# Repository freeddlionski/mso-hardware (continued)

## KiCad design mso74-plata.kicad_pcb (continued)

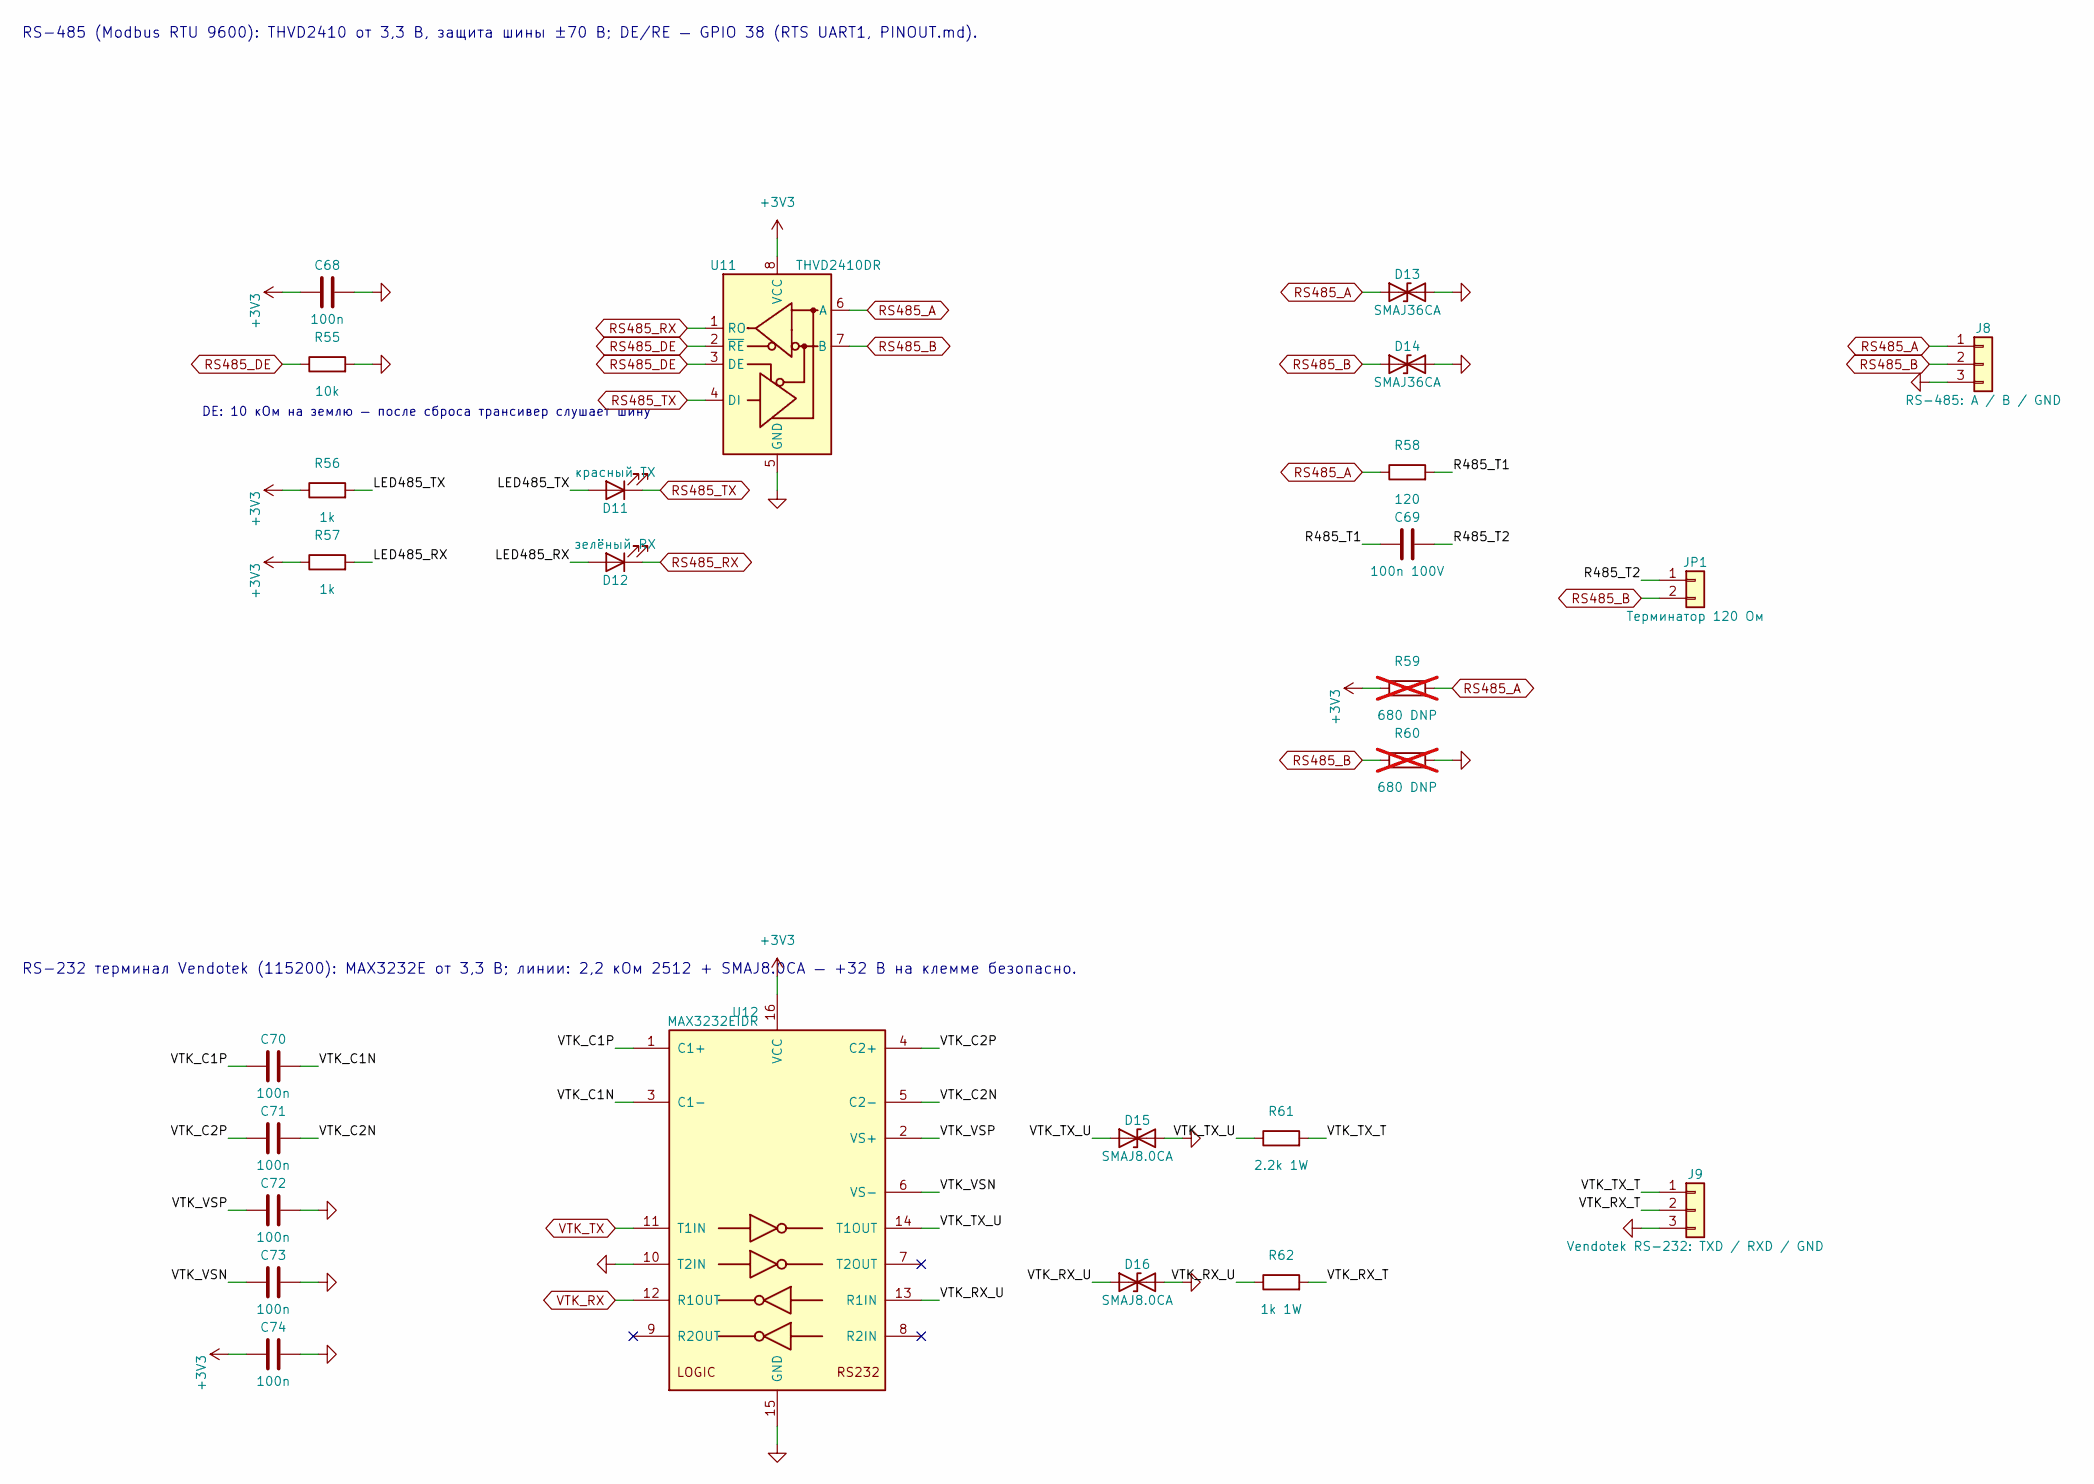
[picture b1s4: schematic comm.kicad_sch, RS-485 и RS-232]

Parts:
C68, C70, C71, C72, C73, C74: 100n; C_0603_1608Metric; MPN CC0603KRX7R9BB104; LCSC C14663
C69: 100n 100V; C_0805_2012Metric; MPN TCC0805X7R104K101DT; LCSC C344180
D11: красный TX; LED_0603_1608Metric; LCSC C2286
D12: зелёный RX; LED_0603_1608Metric; MPN KT-0603YG; LCSC C2289
D13, D14: SMAJ36CA; D_SMA; MPN SMAJ36CA; LCSC C5249597
D15, D16: SMAJ8.0CA; D_SMA; MPN SMAJ8.0CA; LCSC C148237
J8: RS-485: A / B / GND; KANGNEX_WJ15EDGRC_1x03_P3.81mm_Drill1.4; MPN WJ15EDGRC-3.81-03P-14-00A; LCSC C8406
J9: Vendotek RS-232: TXD / RXD / GND; KANGNEX_WJ15EDGRC_1x03_P3.81mm_Drill1.4; MPN WJ15EDGRC-3.81-03P-14-00A; LCSC C8406
JP1: Терминатор 120 Ом; PinHeader_1x02_P2.54mm_Vertical; MPN PZ254V-11-02P; LCSC C492401
R55: 10k; R_0603_1608Metric; MPN 0603WAF1002T5E; LCSC C25804
R56, R57: 1k; R_0603_1608Metric; MPN 0603WAF1001T5E; LCSC C21190
R58: 120; R_0805_2012Metric; MPN 0805W8F1200T5E; LCSC C17437
R59, R60: 680 DNP; R_0603_1608Metric; MPN 0603WAF6800T5E; LCSC C23228; not fitted
R61: 2.2k 1W; R_2512_6332Metric; MPN RC-12K2201FT; LCSC C453411
R62: 1k 1W; R_2512_6332Metric; MPN RC-12K1001FT; LCSC C453362
U11: THVD2410DR; SOIC-8_3.9x4.9mm_P1.27mm; MPN THVD2410DR; LCSC C1849398
U12: MAX3232EIDR; SOIC-16_3.9x9.9mm_P1.27mm; MPN MAX3232EIDR; LCSC C193666

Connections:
+3V3: C68.1, C74.1, R56.1, R57.1, R59.1, U11.8 (VCC), U12.16 (VCC); also elsewhere on the board
/RS-485 и RS-232/LED485_RX: D12.2 (A), R57.2
/RS-485 и RS-232/LED485_TX: D11.2 (A), R56.2
/RS-485 и RS-232/R485_T1: C69.1, R58.2
/RS-485 и RS-232/R485_T2: C69.2, JP1.1
/RS-485 и RS-232/VTK_C1N: C70.2, U12.3 (C1-)
/RS-485 и RS-232/VTK_C1P: C70.1, U12.1 (C1+)
/RS-485 и RS-232/VTK_C2N: C71.2, U12.5 (C2-)
/RS-485 и RS-232/VTK_C2P: C71.1, U12.4 (C2+)
/RS-485 и RS-232/VTK_RX_T: J9.2, R62.2
/RS-485 и RS-232/VTK_RX_U: D16.1 (A1), R62.1, U12.13 (R1IN)
/RS-485 и RS-232/VTK_TX_T: J9.1, R61.2
/RS-485 и RS-232/VTK_TX_U: D15.1 (A1), R61.1, U12.14 (T1OUT)
/RS-485 и RS-232/VTK_VSN: C73.1, U12.6 (VS-)
/RS-485 и RS-232/VTK_VSP: C72.1, U12.2 (VS+)
GND: C68.2, C72.2, C73.2, C74.2, D13.2 (A2), D14.2 (A2), D15.2 (A2), D16.2 (A2), J8.3, J9.3, R55.2, R60.2, U11.5 (GND), U12.10 (T2IN), U12.15 (GND); also elsewhere on the board
RS485_A: D13.1 (A1), J8.1, R58.1, R59.2, U11.6 (A); also elsewhere on the board
RS485_B: D14.1 (A1), J8.2, JP1.2, R60.1, U11.7 (B); also elsewhere on the board
RS485_DE: R55.1, U11.2 (~RE), U11.3 (DE); also elsewhere on the board
RS485_RX: D12.1 (K), U11.1 (RO); also elsewhere on the board
RS485_TX: D11.1 (K), U11.4 (DI); also elsewhere on the board
VTK_RX: U12.12 (R1OUT); also elsewhere on the board
VTK_TX: U12.11 (T1IN); also elsewhere on the board

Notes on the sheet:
RS-485 (Modbus RTU 9600): THVD2410 от 3,3 В, защита шины ±70 В; DE/RE — GPIO 38 (RTS UART1, PINOUT.md).
DE: 10 кОм на землю — после сброса трансивер слушает шину
RS-232 терминал Vendotek (115200): MAX3232E от 3,3 В; линии: 2,2 кОм 2512 + SMAJ8.0CA — +32 В на клемме безопасно.

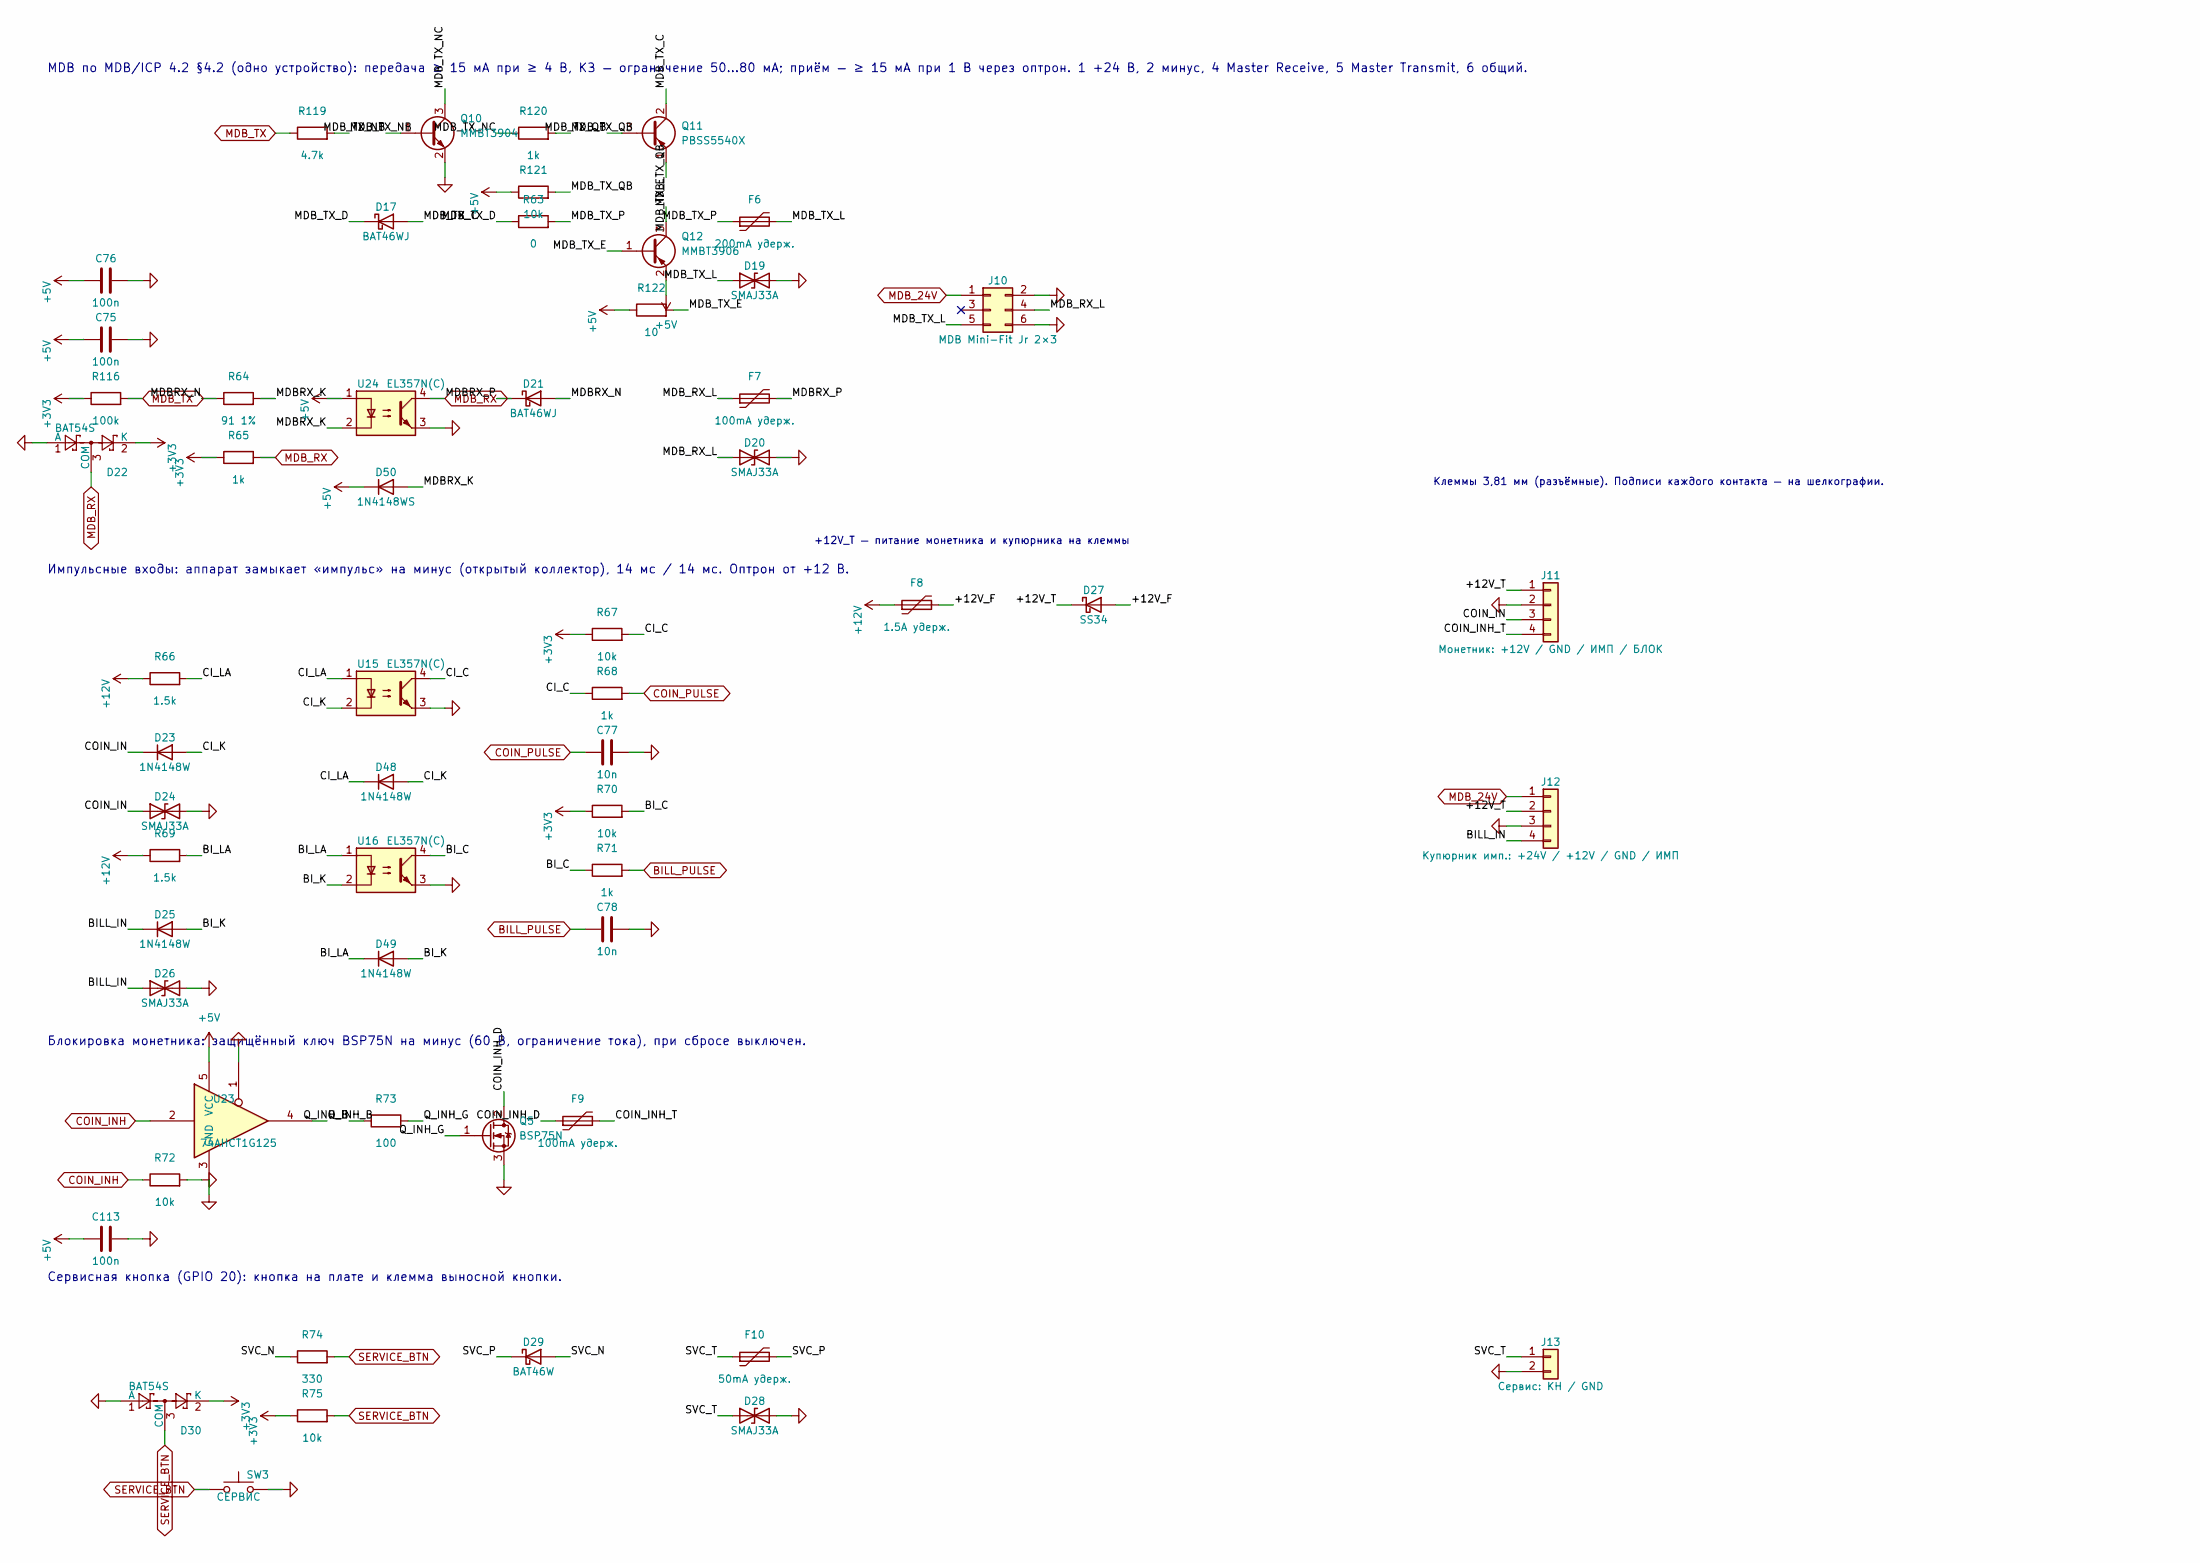
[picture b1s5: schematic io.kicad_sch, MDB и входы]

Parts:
C75, C76, C113: 100n; C_0603_1608Metric; MPN CC0603KRX7R9BB104; LCSC C14663
C77, C78: 10n; C_0603_1608Metric; MPN 0603B103K500NT; LCSC C57112
D17, D21: BAT46WJ; D_SOD-323F; MPN BAT46WJ,115; LCSC C114696
D19, D20, D24, D26, D28: SMAJ33A; D_SMA; MPN SMAJ33A; LCSC C223988
D22, D30: BAT54S; SOT-23; MPN BAT54S; LCSC C47546
D23, D25, D48, D49: 1N4148W; D_SOD-123; MPN 1N4148W; LCSC C81598
D27: SS34; D_SMA; MPN SS34; LCSC C8678
D29: BAT46W; D_SOD-123; MPN BAT46W; LCSC C7420332
D50: 1N4148WS; D_SOD-323; MPN 1N4148WS; LCSC C2128
F6: 200mA удерж.; Fuse_1812_4532Metric; MPN 1812L020/60DR; LCSC C315900
F7, F9: 100mA удерж.; Fuse_1206_3216Metric; MPN nSMD010; LCSC C70065
F8: 1.5A удерж.; Fuse_2920_7451Metric; MPN SMD2920-150/60N; LCSC C6165178
F10: 50mA удерж.; Fuse_1206_3216Metric; MPN 1206L005/60WR; LCSC C315892
J10: MDB Mini-Fit Jr 2×3; Molex_Mini-Fit_Jr_5566-06A_2x03_P4.20mm_Vertical; MPN Molex 5566-06A; LCSC C20539148
J11: Монетник: +12V / GND / ИМП / БЛОК; KANGNEX_WJ15EDGRC_1x04_P3.81mm_Drill1.4; MPN WJ15EDGRC-3.81-04P-14-00A; LCSC C7245
J12: Купюрник имп.: +24V / +12V / GND / ИМП; KANGNEX_WJ15EDGRC_1x04_P3.81mm_Drill1.4; MPN WJ15EDGRC-3.81-04P-14-00A; LCSC C7245
J13: Сервис: КН / GND; KANGNEX_WJ15EDGRC_1x02_P3.81mm_Drill1.4; MPN WJ15EDGRC-3.81-02P-14-00A; LCSC C8387
Q5: BSP75N; SOT-223-3_TabPin3_BSP75N; MPN BSP75N; LCSC C114056
Q10: MMBT3904; SOT-23; MPN MMBT3904; LCSC C20526
Q11: PBSS5540X; SOT-89-3; MPN PBSS5540X,135; LCSC C455078
Q12: MMBT3906; SOT-23; MPN MMBT3906; LCSC C916375
R63: 0; R_0805_2012Metric; MPN 0805W8F0000T5E; LCSC C17477
R64: 91 1%; R_1206_3216Metric; MPN RC1206FR-0791RL; LCSC C137223
R65, R68, R71, R120: 1k; R_0603_1608Metric; MPN 0603WAF1001T5E; LCSC C21190
R66, R69: 1.5k; R_0603_1608Metric; MPN 0603WAF1501T5E; LCSC C22843
R67, R70, R72, R75, R121: 10k; R_0603_1608Metric; MPN 0603WAF1002T5E; LCSC C25804
R73: 100; R_0603_1608Metric; MPN 0603WAF1000T5E; LCSC C22775
R74: 330; R_0603_1608Metric; MPN 0603WAF3300T5E; LCSC C23138
R116: 100k; R_0603_1608Metric; MPN 0603WAF1003T5E; LCSC C25803
R119: 4.7k; R_0603_1608Metric; MPN 0603WAF4701T5E; LCSC C23162
R122: 10; R_0805_2012Metric; MPN 0805W8F100JT5E; LCSC C17415
SW3: СЕРВИС; SW_SPST_TL3342; MPN TL3342F450QG; LCSC C2886897
U15, U16, U24: EL357N(C); SOP-4_3.8x4.1mm_P2.54mm; MPN EL357N(C)-G; LCSC C42379244
U23: 74AHCT1G125; SOT-23-5; MPN SN74AHCT1G125DBVR; LCSC C7484

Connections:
+3V3: D22.2 (K), D30.2 (K), R65.1, R67.1, R70.1, R75.1, R116.1; also elsewhere on the board
+5V: C75.1, C76.1, C113.1, D50.1 (K), Q12.2 (E), R121.1, R122.1, U23.5 (VCC), U24.1; also elsewhere on the board
+12V: F8.1, R66.1, R69.1; also elsewhere on the board
/MDB и входы/+12V_F: D27.2 (A), F8.2
/MDB и входы/+12V_T: D27.1 (K), J11.1, J12.2
/MDB и входы/BILL_IN: D25.1 (K), D26.1 (A1), J12.4
/MDB и входы/BI_C: R70.2, R71.1, U16.4
/MDB и входы/BI_K: D25.2 (A), D49.2 (A), U16.2
/MDB и входы/BI_LA: D49.1 (K), R69.2, U16.1
/MDB и входы/CI_C: R67.2, R68.1, U15.4
/MDB и входы/CI_K: D23.2 (A), D48.2 (A), U15.2
/MDB и входы/CI_LA: D48.1 (K), R66.2, U15.1
/MDB и входы/COIN_IN: D23.1 (K), D24.1 (A1), J11.3
/MDB и входы/COIN_INH_D: F9.1, Q5.2 (D)
/MDB и входы/COIN_INH_T: F9.2, J11.4
/MDB и входы/MDBRX_K: D50.2 (A), R64.2, U24.2
/MDB и входы/MDBRX_N: D21.2 (A), R64.1
/MDB и входы/MDBRX_P: D21.1 (K), F7.2
/MDB и входы/MDB_RX_L: D20.1 (A1), F7.1, J10.4
/MDB и входы/MDB_TX_C: D17.2 (A), Q11.2 (C)
/MDB и входы/MDB_TX_D: D17.1 (K), R63.1
/MDB и входы/MDB_TX_E: Q11.1 (E), Q12.1 (B), R122.2
/MDB и входы/MDB_TX_L: D19.1 (A1), F6.2, J10.5
/MDB и входы/MDB_TX_NB: Q10.1 (B), R119.2
/MDB и входы/MDB_TX_NC: Q10.3 (C), R120.1
/MDB и входы/MDB_TX_P: F6.1, R63.2
/MDB и входы/MDB_TX_QB: Q11.3 (B), Q12.3 (C), R120.2, R121.2
/MDB и входы/Q_INH_B: R73.1, U23.4
/MDB и входы/Q_INH_G: Q5.1 (G), R73.2
/MDB и входы/SVC_N: D29.2 (A), R74.1
/MDB и входы/SVC_P: D29.1 (K), F10.2
/MDB и входы/SVC_T: D28.1 (A1), F10.1, J13.1
BILL_PULSE: C78.1, R71.2; also elsewhere on the board
COIN_INH: R72.1, U23.2; also elsewhere on the board
COIN_PULSE: C77.1, R68.2; also elsewhere on the board
GND: C75.2, C76.2, C77.2, C78.2, C113.2, D19.2 (A2), D20.2 (A2), D22.1 (A), D24.2 (A2), D26.2 (A2), D28.2 (A2), D30.1 (A), J10.2, J10.6, J11.2, J12.3, J13.2, Q5.3 (S), Q10.2 (E), R72.2, SW3.2, U15.3, U16.3, U23.1, U23.3 (GND), U24.3; also elsewhere on the board
MDB_24V: J10.1, J12.1; also elsewhere on the board
MDB_RX: D22.3 (COM), R65.2, U24.4; also elsewhere on the board
MDB_TX: R116.2, R119.1; also elsewhere on the board
SERVICE_BTN: D30.3 (COM), R74.2, R75.2, SW3.1; also elsewhere on the board

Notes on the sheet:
MDB по MDB/ICP 4.2 §4.2 (одно устройство): передача ≥ 15 мА при ≥ 4 В, КЗ — ограничение 50…80 мА; приём — ≥ 15 мА при 1 В через оптрон. 1 +24 В, 2 минус, 4 Master Receive, 5 Master Transmit, 6 общий.
Импульсные входы: аппарат замыкает «импульс» на минус (открытый коллектор), 14 мс / 14 мс. Оптрон от +12 В.
+12V_T — питание монетника и купюрника на клеммы
Блокировка монетника: защищённый ключ BSP75N на минус (60 В, ограничение тока), при сбросе выключен.
Сервисная кнопка (GPIO 20): кнопка на плате и клемма выносной кнопки.
Клеммы 3,81 мм (разъёмные). Подписи каждого контакта — на шелкографии.

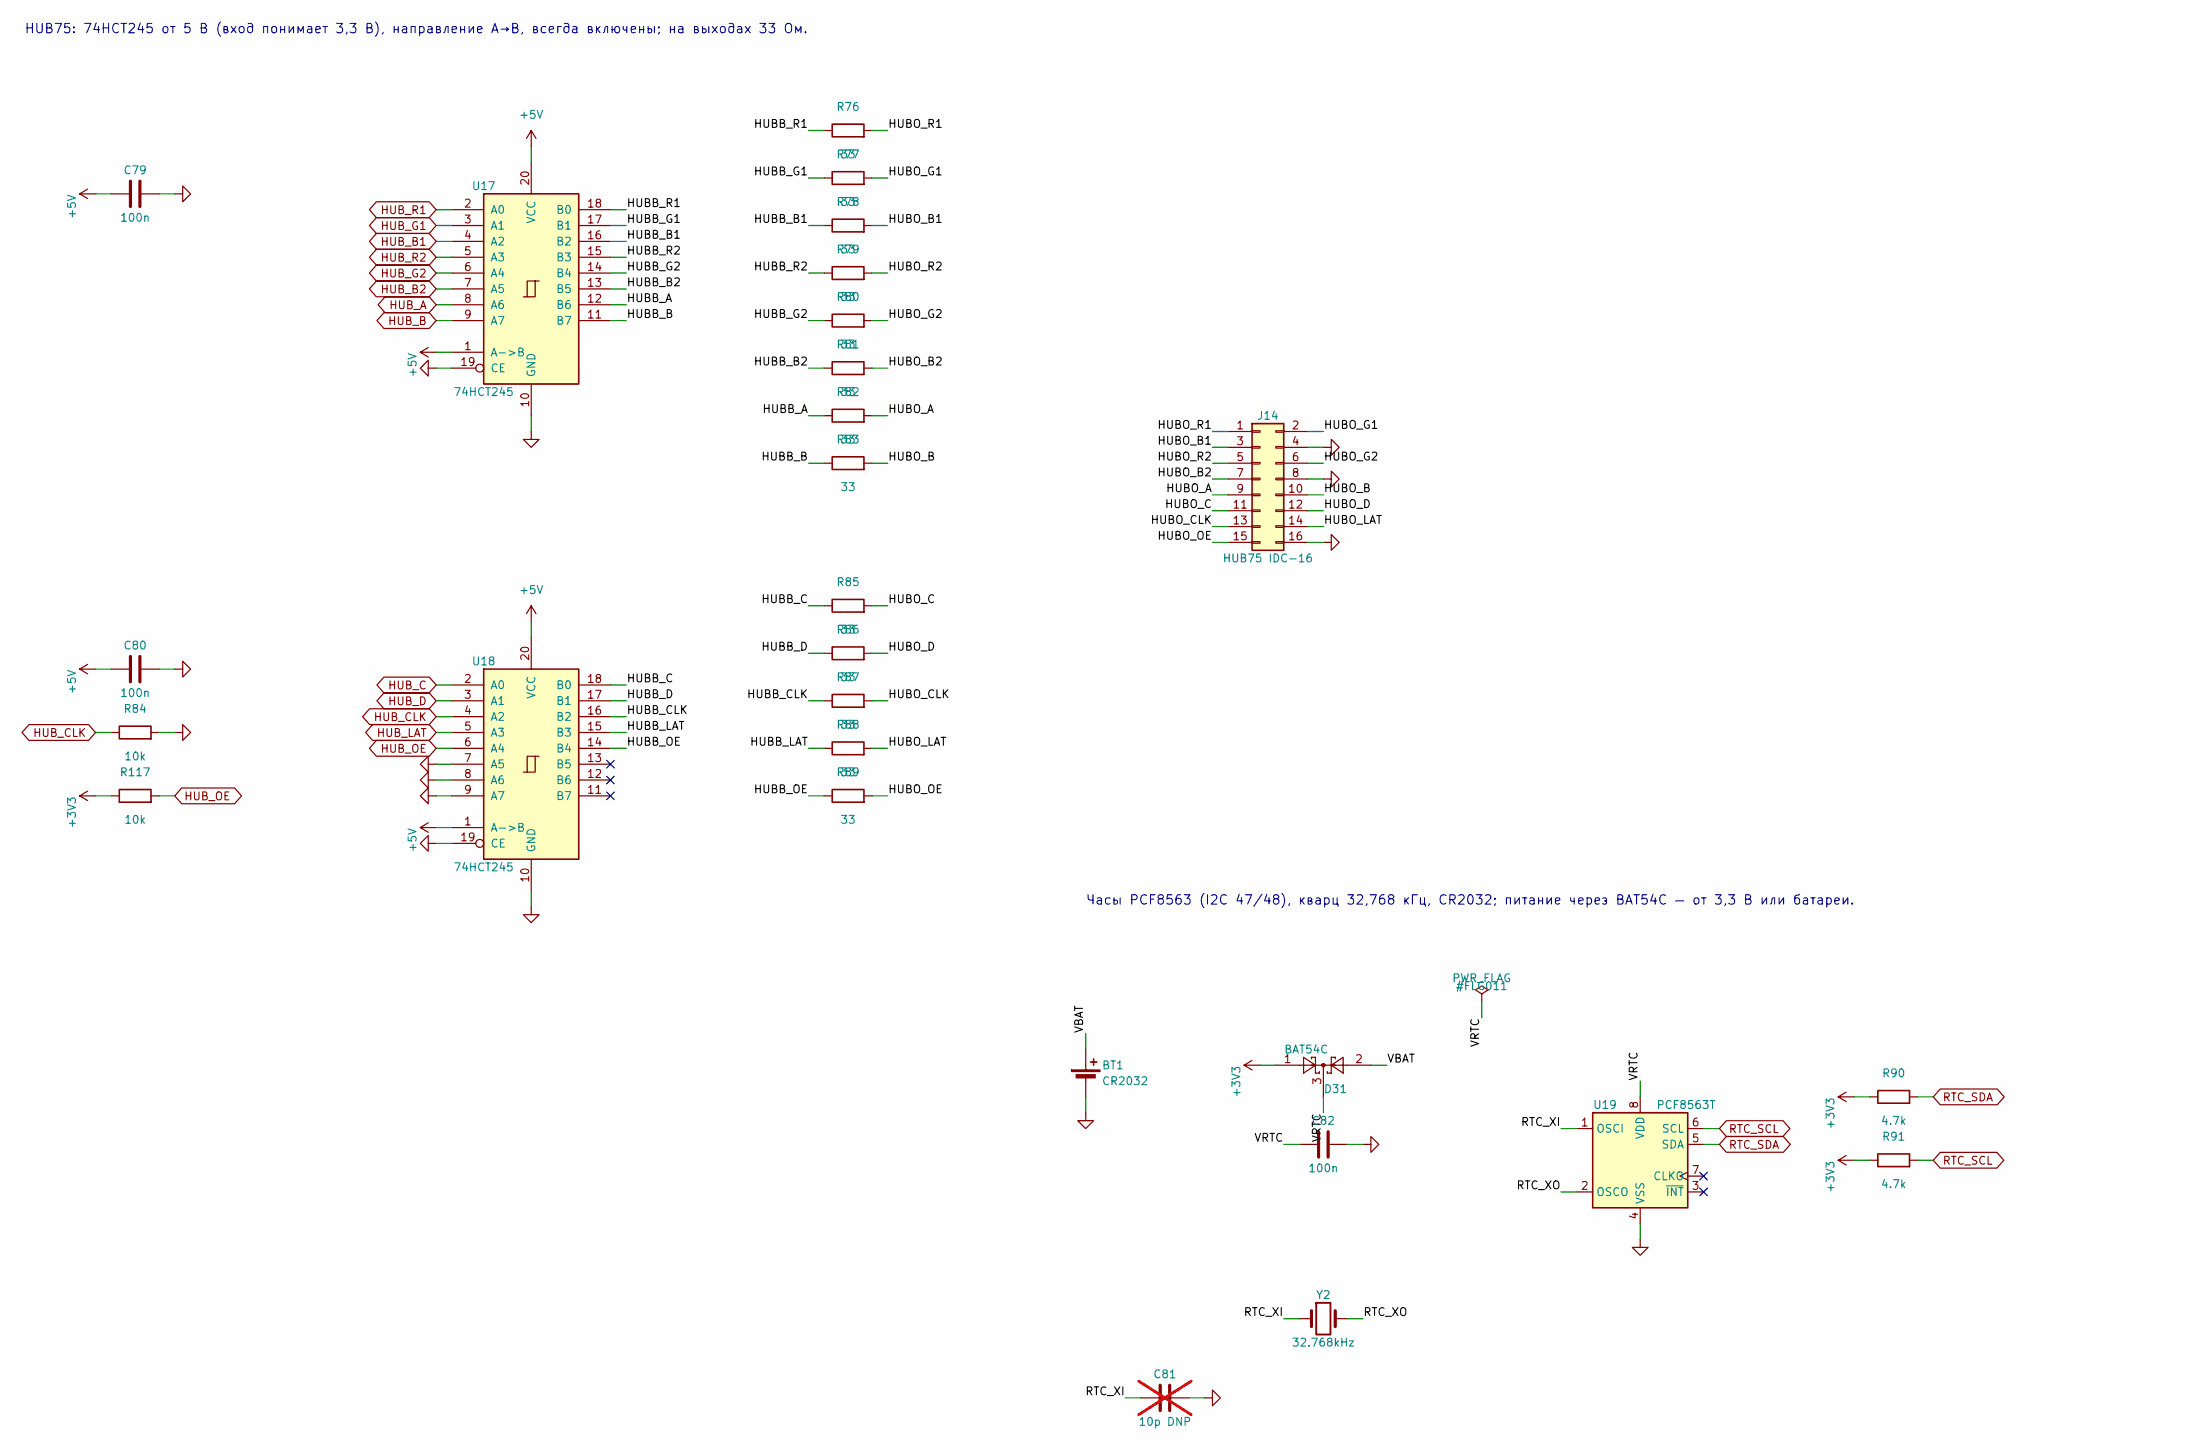
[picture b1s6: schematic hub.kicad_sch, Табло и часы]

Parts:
BT1: CR2032; BatteryHolder_MYOUNG_BS-07-A1BJ001_CR2032; MPN BS-07-A1BJ001; LCSC C2979167
C79, C80, C82: 100n; C_0603_1608Metric; MPN CC0603KRX7R9BB104; LCSC C14663
C81: 10p DNP; C_0603_1608Metric; MPN CL10C100JB8NNNC; LCSC C1634; not fitted
D31: BAT54C; SOT-23; MPN BAT54C; LCSC C2135
J14: HUB75 IDC-16; IDC-Header_2x08_P2.54mm_Vertical; MPN 2.54-2*8P box header; LCSC C3406
R76, R77, R78, R79, R80, R81, R82, R83, R85, R86, R87, R88, R89: 33; R_0603_1608Metric; MPN 0603WAF330JT5E; LCSC C23140
R84, R117: 10k; R_0603_1608Metric; MPN 0603WAF1002T5E; LCSC C25804
R90, R91: 4.7k; R_0603_1608Metric; MPN 0603WAF4701T5E; LCSC C23162
U17, U18: 74HCT245; TSSOP-20_4.4x6.5mm_P0.65mm; MPN 74HCT245PW; LCSC C5980
U19: PCF8563T; SOIC-8_3.9x4.9mm_P1.27mm; MPN PCF8563T/5; LCSC C7440
Y2: 32.768kHz; Crystal_SMD_3215-2Pin_3.2x1.5mm; MPN Q13FC13500004; LCSC C32346

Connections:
+3V3: D31.1, R90.1, R91.1, R117.1; also elsewhere on the board
+5V: C79.1, C80.1, U17.1 (A->B), U17.20 (VCC), U18.1 (A->B), U18.20 (VCC); also elsewhere on the board
/Табло и часы/HUBB_A: R82.1, U17.12 (B6)
/Табло и часы/HUBB_B: R83.1, U17.11 (B7)
/Табло и часы/HUBB_B1: R78.1, U17.16 (B2)
/Табло и часы/HUBB_B2: R81.1, U17.13 (B5)
/Табло и часы/HUBB_C: R85.1, U18.18 (B0)
/Табло и часы/HUBB_CLK: R87.1, U18.16 (B2)
/Табло и часы/HUBB_D: R86.1, U18.17 (B1)
/Табло и часы/HUBB_G1: R77.1, U17.17 (B1)
/Табло и часы/HUBB_G2: R80.1, U17.14 (B4)
/Табло и часы/HUBB_LAT: R88.1, U18.15 (B3)
/Табло и часы/HUBB_OE: R89.1, U18.14 (B4)
/Табло и часы/HUBB_R1: R76.1, U17.18 (B0)
/Табло и часы/HUBB_R2: R79.1, U17.15 (B3)
/Табло и часы/HUBO_A: J14.9, R82.2
/Табло и часы/HUBO_B: J14.10, R83.2
/Табло и часы/HUBO_B1: J14.3, R78.2
/Табло и часы/HUBO_B2: J14.7, R81.2
/Табло и часы/HUBO_C: J14.11, R85.2
/Табло и часы/HUBO_CLK: J14.13, R87.2
/Табло и часы/HUBO_D: J14.12, R86.2
/Табло и часы/HUBO_G1: J14.2, R77.2
/Табло и часы/HUBO_G2: J14.6, R80.2
/Табло и часы/HUBO_LAT: J14.14, R88.2
/Табло и часы/HUBO_OE: J14.15, R89.2
/Табло и часы/HUBO_R1: J14.1, R76.2
/Табло и часы/HUBO_R2: J14.5, R79.2
/Табло и часы/RTC_XI: C81.1, U19.1 (OSCI), Y2.1
/Табло и часы/RTC_XO: U19.2 (OSCO), Y2.2
/Табло и часы/VBAT: BT1.1 (+), D31.2
/Табло и часы/VRTC: C82.1, D31.3, U19.8 (VDD)
GND: BT1.2 (-), C79.2, C80.2, C81.2, C82.2, J14.4, J14.8, J14.16, R84.2, U17.10 (GND), U17.19 (CE), U18.7 (A5), U18.8 (A6), U18.9 (A7), U18.10 (GND), U18.19 (CE), U19.4 (VSS); also elsewhere on the board
HUB_A: U17.8 (A6); also elsewhere on the board
HUB_B: U17.9 (A7); also elsewhere on the board
HUB_B1: U17.4 (A2); also elsewhere on the board
HUB_B2: U17.7 (A5); also elsewhere on the board
HUB_C: U18.2 (A0); also elsewhere on the board
HUB_CLK: R84.1, U18.4 (A2); also elsewhere on the board
HUB_D: U18.3 (A1); also elsewhere on the board
HUB_G1: U17.3 (A1); also elsewhere on the board
HUB_G2: U17.6 (A4); also elsewhere on the board
HUB_LAT: U18.5 (A3); also elsewhere on the board
HUB_OE: R117.2, U18.6 (A4); also elsewhere on the board
HUB_R1: U17.2 (A0); also elsewhere on the board
HUB_R2: U17.5 (A3); also elsewhere on the board
RTC_SCL: R91.2, U19.6 (SCL); also elsewhere on the board
RTC_SDA: R90.2, U19.5 (SDA); also elsewhere on the board

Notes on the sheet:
HUB75: 74HCT245 от 5 В (вход понимает 3,3 В), направление A→B, всегда включены; на выходах 33 Ом.
Часы PCF8563 (I2C 47/48), кварц 32,768 кГц, CR2032; питание через BAT54C — от 3,3 В или батареи.

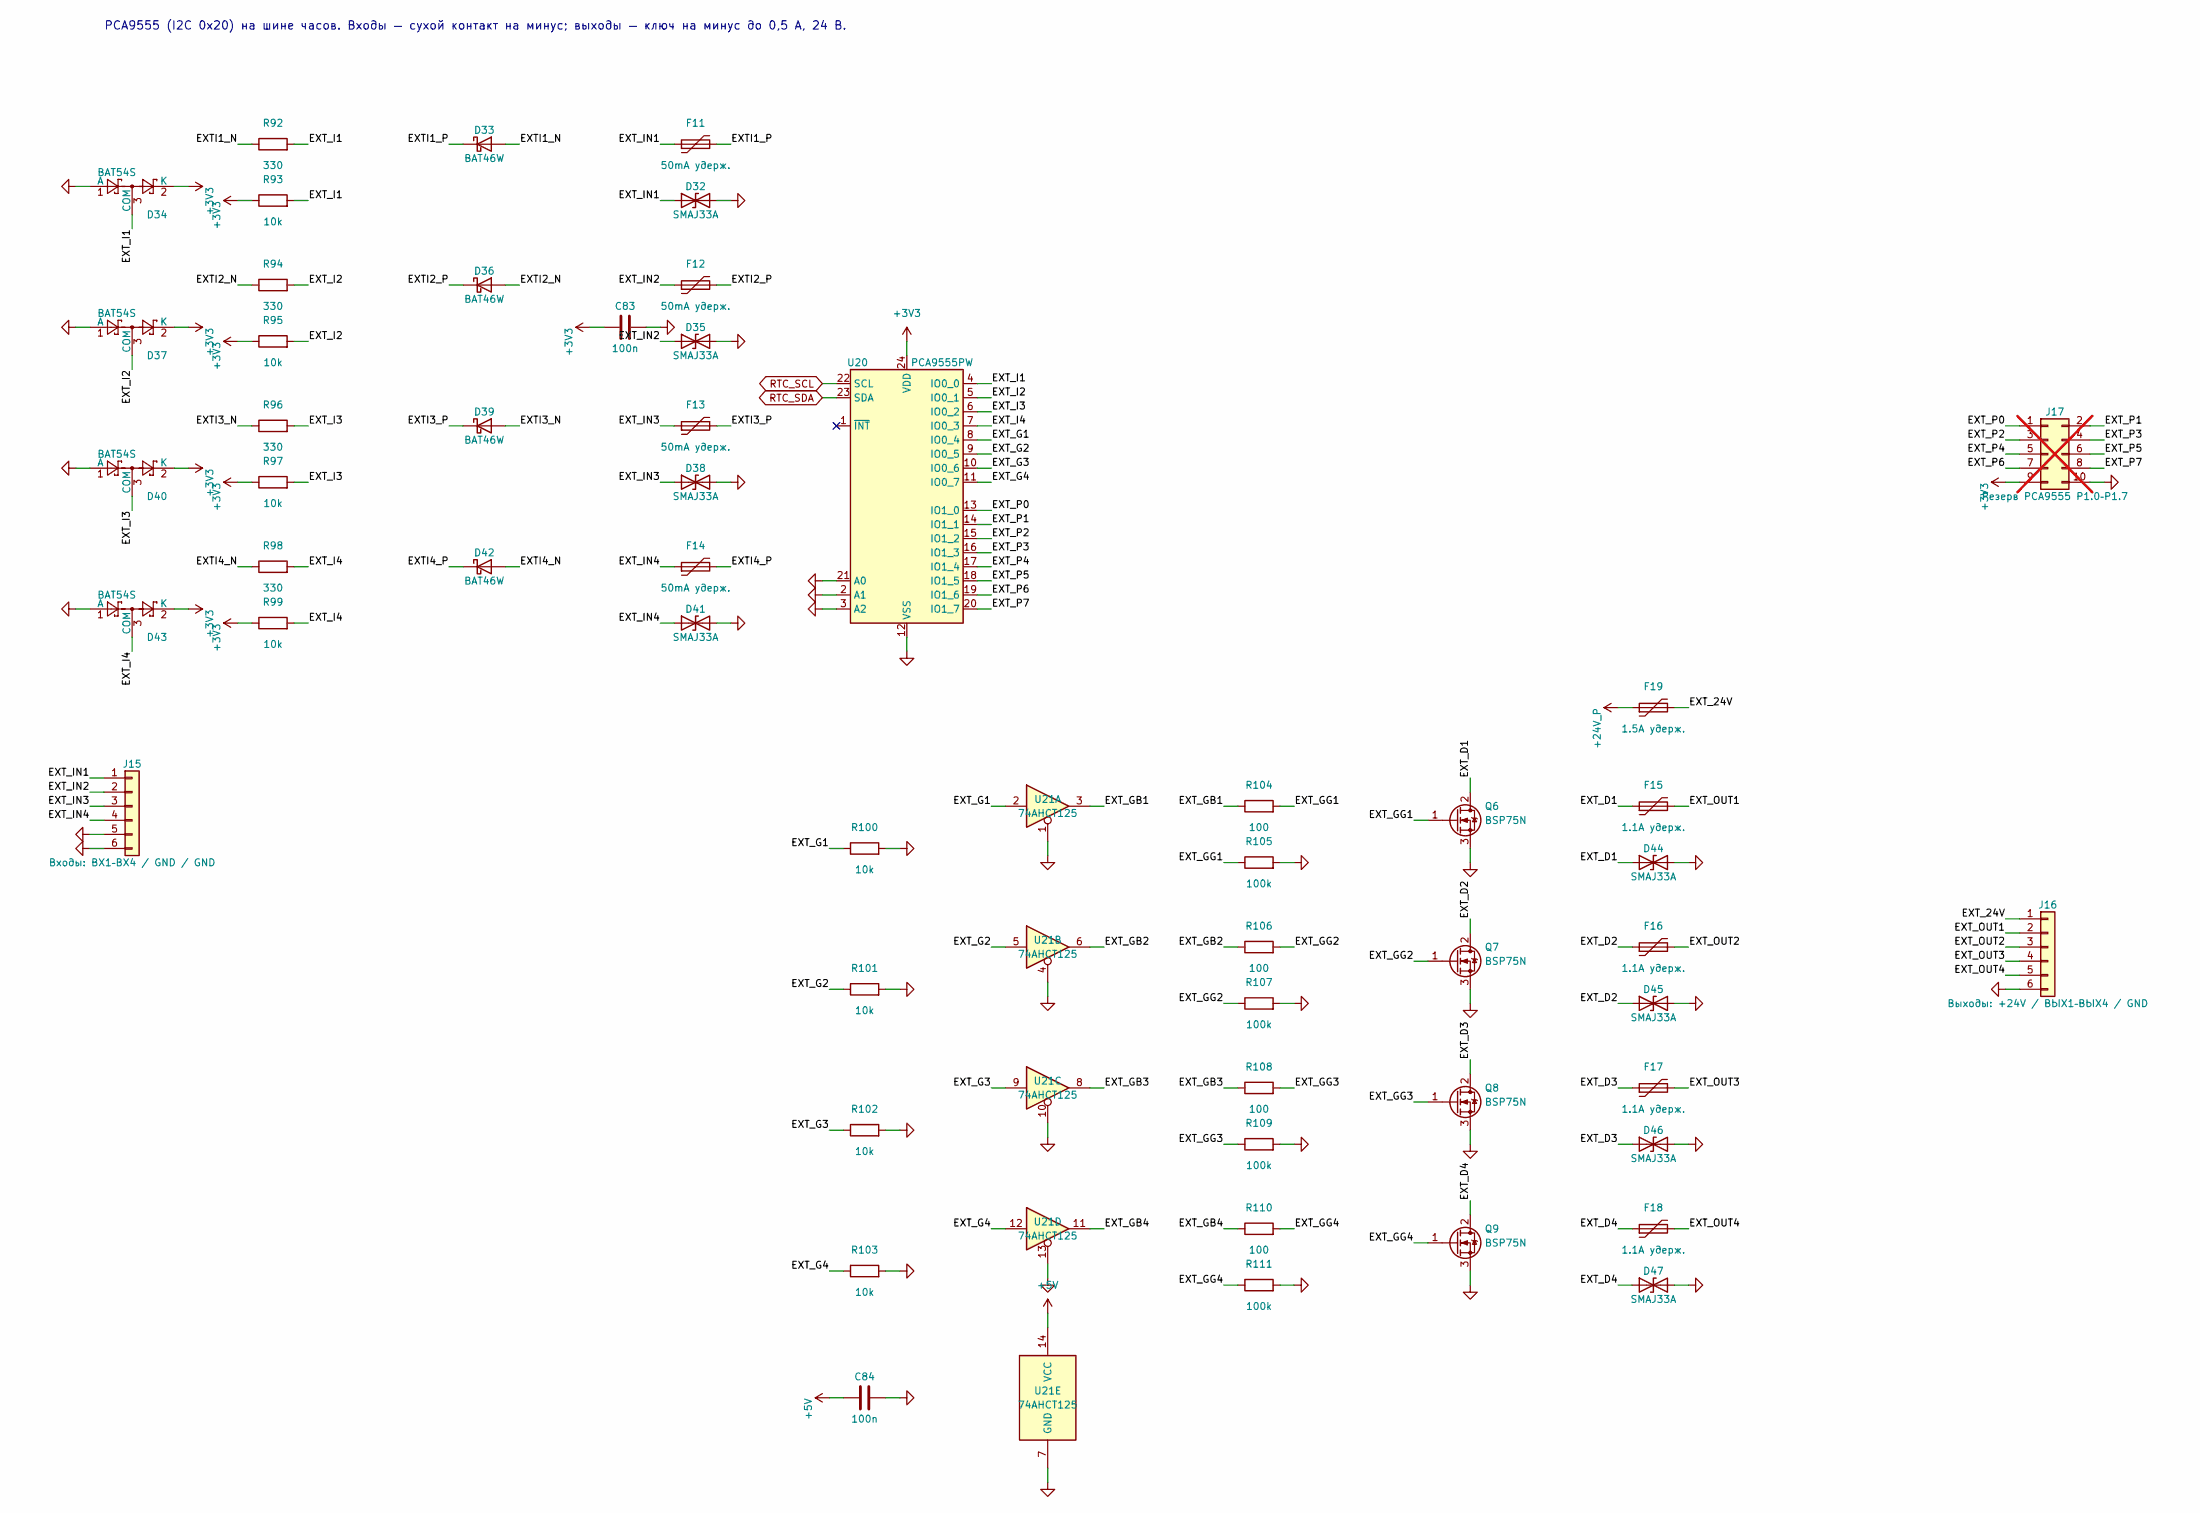
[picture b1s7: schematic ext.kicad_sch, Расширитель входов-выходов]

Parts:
C83, C84: 100n; C_0603_1608Metric; MPN CC0603KRX7R9BB104; LCSC C14663
D32, D35, D38, D41, D44, D45, D46, D47: SMAJ33A; D_SMA; MPN SMAJ33A; LCSC C223988
D33, D36, D39, D42: BAT46W; D_SOD-123; MPN BAT46W; LCSC C7420332
D34, D37, D40, D43: BAT54S; SOT-23; MPN BAT54S; LCSC C47546
F11, F12, F13, F14: 50mA удерж.; Fuse_1206_3216Metric; MPN 1206L005/60WR; LCSC C315892
F15, F16, F17, F18: 1.1A удерж.; Fuse_2920_7451Metric; MPN 2920L110/60MR; LCSC C315903
F19: 1.5A удерж.; Fuse_2920_7451Metric; MPN SMD2920-150/60N; LCSC C6165178
J15: Входы: ВХ1–ВХ4 / GND / GND; KANGNEX_WJ15EDGRC_1x06_P3.81mm_Drill1.4; MPN WJ15EDGRC-3.81-06P-14-00A; LCSC C7246
J16: Выходы: +24V / ВЫХ1–ВЫХ4 / GND; KANGNEX_WJ15EDGRC_1x06_P3.81mm_Drill1.4; MPN WJ15EDGRC-3.81-06P-14-00A; LCSC C7246
J17: Резерв PCA9555 P1.0–P1.7; PinHeader_2x05_P2.54mm_Vertical; MPN PZ254V-12-10P; LCSC C492422; not fitted
Q6, Q7, Q8, Q9: BSP75N; SOT-223-3_TabPin3_BSP75N; MPN BSP75N; LCSC C114056
R92, R94, R96, R98: 330; R_0603_1608Metric; MPN 0603WAF3300T5E; LCSC C23138
R93, R95, R97, R99, R100, R101, R102, R103: 10k; R_0603_1608Metric; MPN 0603WAF1002T5E; LCSC C25804
R104, R106, R108, R110: 100; R_0603_1608Metric; MPN 0603WAF1000T5E; LCSC C22775
R105, R107, R109, R111: 100k; R_0603_1608Metric; MPN 0603WAF1003T5E; LCSC C25803
U20: PCA9555PW; TSSOP-24_4.4x7.8mm_P0.65mm; MPN PCA9555PW; LCSC C128392
U21: 74AHCT125; TSSOP-14_4.4x5mm_P0.65mm; MPN 74AHCT125PW; LCSC C176917

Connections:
+3V3: C83.1, D34.2 (K), D37.2 (K), D40.2 (K), D43.2 (K), J17.9, R93.1, R95.1, R97.1, R99.1, U20.24 (VDD); also elsewhere on the board
+5V: C84.1, U21.14 (VCC); also elsewhere on the board
+24V_P: F19.1; also elsewhere on the board
/Расширитель входов-выходов/EXTI1_N: D33.2 (A), R92.1
/Расширитель входов-выходов/EXTI1_P: D33.1 (K), F11.2
/Расширитель входов-выходов/EXTI2_N: D36.2 (A), R94.1
/Расширитель входов-выходов/EXTI2_P: D36.1 (K), F12.2
/Расширитель входов-выходов/EXTI3_N: D39.2 (A), R96.1
/Расширитель входов-выходов/EXTI3_P: D39.1 (K), F13.2
/Расширитель входов-выходов/EXTI4_N: D42.2 (A), R98.1
/Расширитель входов-выходов/EXTI4_P: D42.1 (K), F14.2
/Расширитель входов-выходов/EXT_24V: F19.2, J16.1
/Расширитель входов-выходов/EXT_D1: D44.1 (A1), F15.1, Q6.2 (D)
/Расширитель входов-выходов/EXT_D2: D45.1 (A1), F16.1, Q7.2 (D)
/Расширитель входов-выходов/EXT_D3: D46.1 (A1), F17.1, Q8.2 (D)
/Расширитель входов-выходов/EXT_D4: D47.1 (A1), F18.1, Q9.2 (D)
/Расширитель входов-выходов/EXT_G1: R100.1, U20.8 (IO0_4), U21.2
/Расширитель входов-выходов/EXT_G2: R101.1, U20.9 (IO0_5), U21.5
/Расширитель входов-выходов/EXT_G3: R102.1, U20.10 (IO0_6), U21.9
/Расширитель входов-выходов/EXT_G4: R103.1, U20.11 (IO0_7), U21.12
/Расширитель входов-выходов/EXT_GB1: R104.1, U21.3
/Расширитель входов-выходов/EXT_GB2: R106.1, U21.6
/Расширитель входов-выходов/EXT_GB3: R108.1, U21.8
/Расширитель входов-выходов/EXT_GB4: R110.1, U21.11
/Расширитель входов-выходов/EXT_GG1: Q6.1 (G), R104.2, R105.1
/Расширитель входов-выходов/EXT_GG2: Q7.1 (G), R106.2, R107.1
/Расширитель входов-выходов/EXT_GG3: Q8.1 (G), R108.2, R109.1
/Расширитель входов-выходов/EXT_GG4: Q9.1 (G), R110.2, R111.1
/Расширитель входов-выходов/EXT_I1: D34.3 (COM), R92.2, R93.2, U20.4 (IO0_0)
/Расширитель входов-выходов/EXT_I2: D37.3 (COM), R94.2, R95.2, U20.5 (IO0_1)
/Расширитель входов-выходов/EXT_I3: D40.3 (COM), R96.2, R97.2, U20.6 (IO0_2)
/Расширитель входов-выходов/EXT_I4: D43.3 (COM), R98.2, R99.2, U20.7 (IO0_3)
/Расширитель входов-выходов/EXT_IN1: D32.1 (A1), F11.1, J15.1
/Расширитель входов-выходов/EXT_IN2: D35.1 (A1), F12.1, J15.2
/Расширитель входов-выходов/EXT_IN3: D38.1 (A1), F13.1, J15.3
/Расширитель входов-выходов/EXT_IN4: D41.1 (A1), F14.1, J15.4
/Расширитель входов-выходов/EXT_OUT1: F15.2, J16.2
/Расширитель входов-выходов/EXT_OUT2: F16.2, J16.3
/Расширитель входов-выходов/EXT_OUT3: F17.2, J16.4
/Расширитель входов-выходов/EXT_OUT4: F18.2, J16.5
/Расширитель входов-выходов/EXT_P0: J17.1, U20.13 (IO1_0)
/Расширитель входов-выходов/EXT_P1: J17.2, U20.14 (IO1_1)
/Расширитель входов-выходов/EXT_P2: J17.3, U20.15 (IO1_2)
/Расширитель входов-выходов/EXT_P3: J17.4, U20.16 (IO1_3)
/Расширитель входов-выходов/EXT_P4: J17.5, U20.17 (IO1_4)
/Расширитель входов-выходов/EXT_P5: J17.6, U20.18 (IO1_5)
/Расширитель входов-выходов/EXT_P6: J17.7, U20.19 (IO1_6)
/Расширитель входов-выходов/EXT_P7: J17.8, U20.20 (IO1_7)
GND: C83.2, C84.2, D32.2 (A2), D34.1 (A), D35.2 (A2), D37.1 (A), D38.2 (A2), D40.1 (A), D41.2 (A2), D43.1 (A), D44.2 (A2), D45.2 (A2), D46.2 (A2), D47.2 (A2), J15.5, J15.6, J16.6, J17.10, Q6.3 (S), Q7.3 (S), Q8.3 (S), Q9.3 (S), R100.2, R101.2, R102.2, R103.2, R105.2, R107.2, R109.2, R111.2, U20.2 (A1), U20.3 (A2), U20.12 (VSS), U20.21 (A0), U21.1, U21.4, U21.7 (GND), U21.10, U21.13; also elsewhere on the board
RTC_SCL: U20.22 (SCL); also elsewhere on the board
RTC_SDA: U20.23 (SDA); also elsewhere on the board

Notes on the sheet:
PCA9555 (I2C 0x20) на шине часов. Входы — сухой контакт на минус; выходы — ключ на минус до 0,5 А, 24 В.
